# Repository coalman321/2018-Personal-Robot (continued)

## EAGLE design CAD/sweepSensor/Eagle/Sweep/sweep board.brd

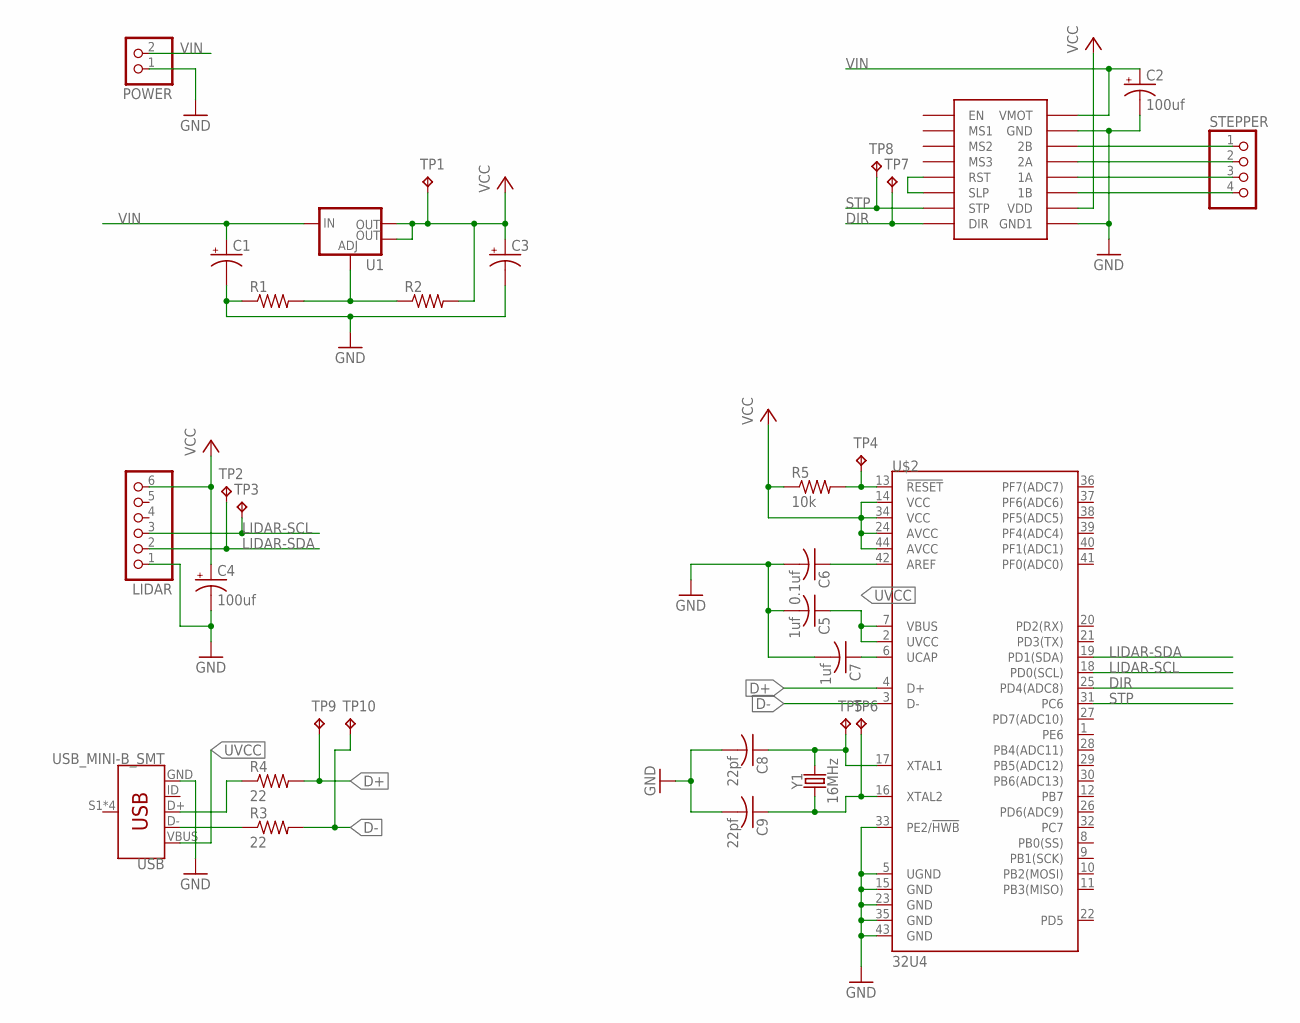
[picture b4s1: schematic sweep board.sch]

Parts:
C1: CPOL-USE2-5; E2-5
C2, C4: 100uf; E3,5-8
C3: CPOL-USE3.5-8; E3,5-8
C5, C7: 1uf; C0603
C6: 0.1uf; C0603
C8, C9: 22pf; C0603
LIDAR: PINHD-1X6; 1X06
POWER: PINHD-1X2; 1X02
R1, R2: R-US_R0603; R0603
R3, R4: 22; R0603
R5: 10k; R0603
STEPPER: PINHD-1X4; 1X04
TP1, TP2, TP3, TP4, TP5, TP6, TP7, TP8, TP9, TP10: TPB1,27; B1,27
U1: V_REG_LM1117SOT223; SOT223
U$1: A4988
U$2: 32U4; TQFP44
USB: USB_MINI-B_SMT; USB-MINIB
Y1: 16MHz; CRYSTAL-SMD-5X3.2-4PAD

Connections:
D+: R4.2, TP9.TP, U$2.4 (D+)
D-: R3.2, TP10.TP, U$2.3 (D-)
DIR: TP7.TP, U$1.P$8 (DIR), U$2.25 (PD4(ADC8))
GND: C1.-, C2.-, C3.-, C4.-, C5.2, C6.2, C7.2, C8.2, C9.2, LIDAR.1, POWER.1, R1.1, U$1.P$10 (GND), U$1.P$16 (GND1), U$2.5 (UGND), U$2.15 (GND), U$2.23 (GND), U$2.33 (PE2/!HWB), U$2.35 (GND), U$2.43 (GND), USB.GND
LIDAR-SCL: LIDAR.3, TP3.TP, U$2.18 (PD0(SCL))
LIDAR-SDA: LIDAR.2, TP2.TP, U$2.19 (PD1(SDA))
unnamed: U$1.P$5 (RST), U$1.P$6 (SLP)
unnamed: STEPPER.4, U$1.P$14 (1B)
unnamed: STEPPER.3, U$1.P$13 (1A)
unnamed: STEPPER.2, U$1.P$12 (2A)
unnamed: STEPPER.1, U$1.P$11 (2B)
unnamed: R3.1, USB.D-
unnamed: R4.1, USB.D+
unnamed: R1.2, R2.1, U1.1 (ADJ)
unnamed: R5.2, TP4.TP, U$2.13 (!RESET)
unnamed: C6.1, U$2.42 (AREF)
unnamed: C7.1, U$2.6 (UCAP)
unnamed: C9.1, TP6.TP, U$2.16 (XTAL2), Y1.1
unnamed: C8.1, TP5.TP, U$2.17 (XTAL1), Y1.3 (2)
STP: TP8.TP, U$1.P$7 (STP), U$2.31 (PC6)
UVCC: C5.1, U$2.2 (UVCC), U$2.7 (VBUS), USB.VBUS
VCC: C3.+, C4.+, LIDAR.6, R2.2, R5.1, TP1.TP, U1.2 (OUT), U1.4 (OUT), U$1.P$15 (VDD), U$2.14 (VCC), U$2.24 (AVCC), U$2.34 (VCC), U$2.44 (AVCC)
VIN: C1.+, C2.+, POWER.2, U1.3 (IN), U$1.P$9 (VMOT)

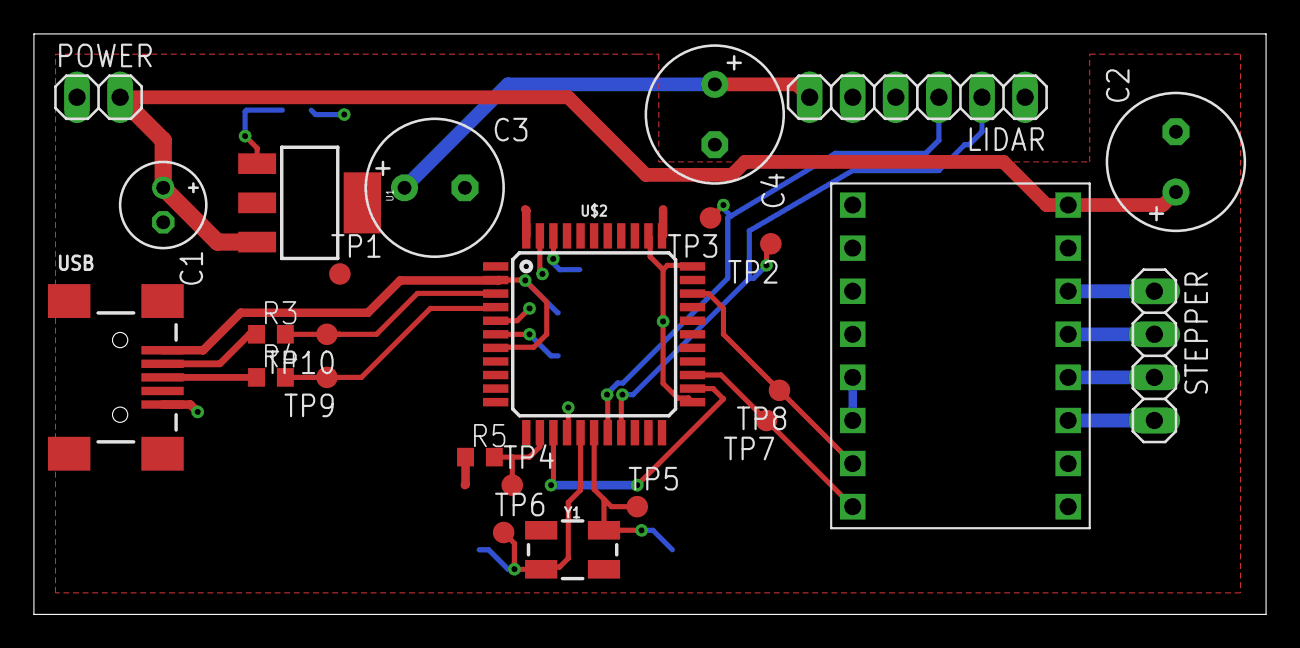
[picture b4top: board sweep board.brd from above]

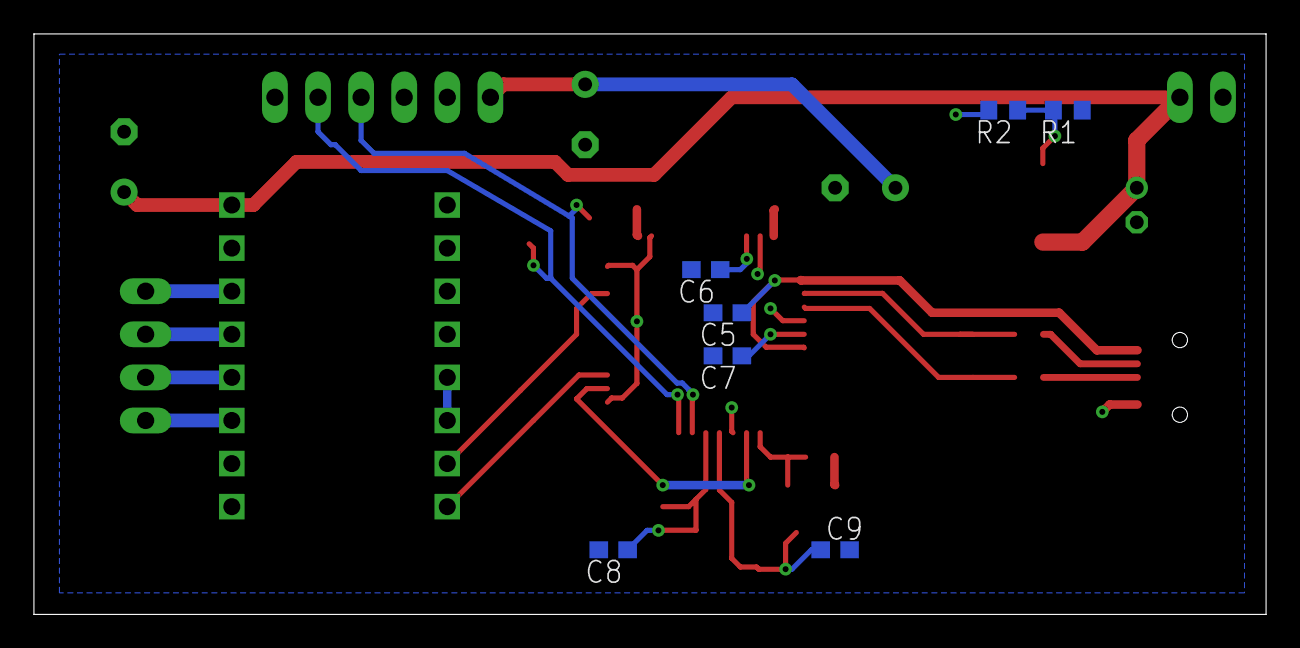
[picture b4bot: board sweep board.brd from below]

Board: 2 copper layers, 72.6 x 34.2 mm, 32 parts (7 on the bottom side), 23 nets.

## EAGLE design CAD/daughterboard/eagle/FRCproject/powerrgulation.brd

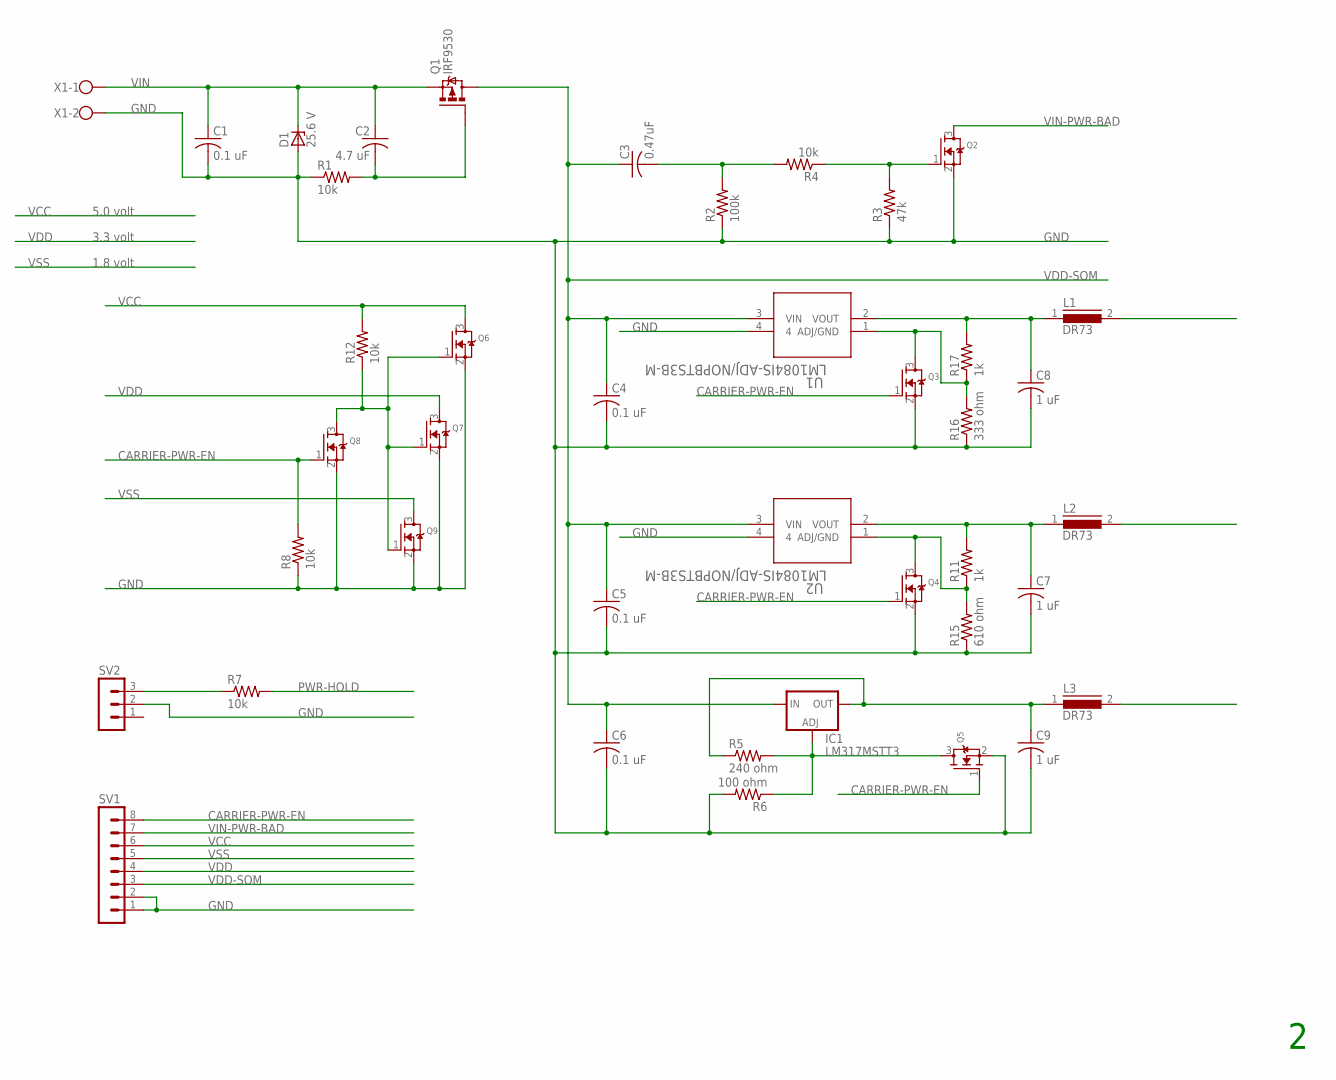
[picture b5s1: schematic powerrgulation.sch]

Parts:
C1, C4, C5, C6: 0.1 uF; C0805
C2: 4.7 uF; C0805
C3: 0.47uF; C0805
C7, C8, C9: 1 uF; C0805
D1: 25.6 V; SOT23
IC1: LM317MSTT3; SOT223
L1, L2, L3: DR73
Q1: IRF9530; TO220BV
Q2, Q3, Q4, Q5, Q6, Q7, Q8, Q9: MOSFET-NREFLOW; SOT23
R1, R4, R7, R8, R12: 10k; R0603
R2: 100k; R0603
R3: 47k; R0603
R5: 240 ohm; R0603
R6: 100 ohm; R0603
R11, R17: 1k; R0603
R15: 610 ohm; R0603
R16: 333 ohm; R0603
SV1: MA08-1
SV2: MA03-1
U1, U2: LM1084IS-ADJ/NOPBTS3B-M; TS3B-M
X1: W237-102

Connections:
CARRIER-PWR-EN: Q3.1 (G), Q4.1 (G), Q5.1 (G), Q8.1 (G), R8.2, SV1.8
GND: C1.2, C4.2, C5.2, C6.2, C7.2, C8.2, C9.2, D1.1 (A), Q2.2 (S), Q3.2 (S), Q4.2 (S), Q5.2 (S), Q6.2 (S), Q7.2 (S), Q8.2 (S), Q9.2 (S), R1.1, R2.1, R3.1, R6.2, R8.1, R15.1, R16.1, SV1.1, SV1.2, SV2.2, U1.4, U2.4, X1.2
unnamed: R7.1, SV2.3
unnamed: C3.2, R2.2, R4.2
unnamed: Q2.1 (G), R3.2, R4.1
unnamed: IC1.1 (ADJ), Q5.3 (D), R5.2, R6.1
unnamed: Q3.3 (D), R16.2, R17.1, U1.1 (ADJ/GND)
unnamed: Q4.3 (D), R11.1, R15.2, U2.1 (ADJ/GND)
PWR-HOLD: C2.2, Q1.G, R1.2, R7.2
RAIL-DISCHARGE: Q6.1 (G), Q7.1 (G), Q8.3 (D), Q9.1 (G), R12.1
VCC: L1.2, Q6.3 (D), R12.2, SV1.6
VCC-VOUT: C8.1, L1.1, R17.2, U1.2 (VOUT)
VDD: L2.2, Q7.3 (D), SV1.4
VDD-SOM: C3.1, C4.1, C5.1, C6.1, IC1.3 (IN), Q1.D, SV1.3, U1.3 (VIN), U2.3 (VIN)
VDD-VOUT: C7.1, L2.1, R11.2, U2.2 (VOUT)
VIN: C1.1, C2.1, D1.3 (C), Q1.S, X1.1
VIN-PWR-BAD: Q2.3 (D), SV1.7
VSS: L3.2, Q9.3 (D), SV1.5
VSS-VOUT: C9.1, IC1.4 (OUT), L3.1, R5.1

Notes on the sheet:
1.8 volt
3.3 volt
5.0 volt

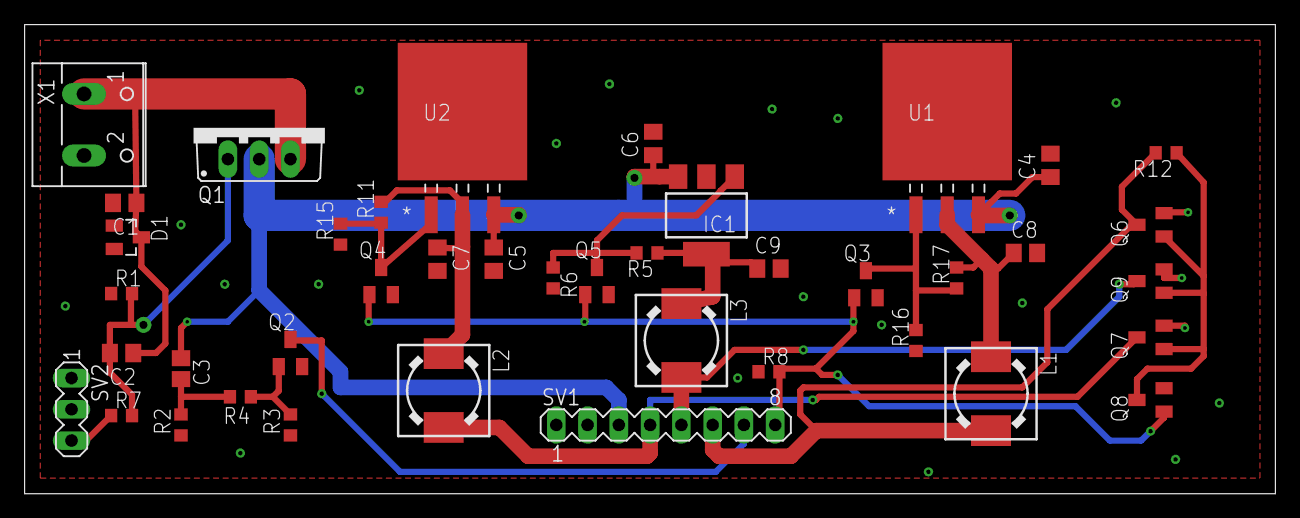
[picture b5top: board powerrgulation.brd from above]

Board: 2 copper layers, 101.6 x 38.1 mm, 41 parts (0 on the bottom side), 19 nets.

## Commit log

2018-05-23 added base project
2018-05-23 added PP code
2018-05-23 made logging system more robust for application
2018-05-25 minor patches
2018-05-26 setting up codebase
2018-08-07 added sim
2018-08-08 re-working rio code
2018-08-08 added beta code
2018-08-09 switching to 2018 system
2018-08-09 whaaaa
2018-08-09 project compiles
2018-08-09 compiles and tests!
2018-08-09 add subsystem manager
2018-08-10 ive got a theory. now to test its foundation
2018-08-11 removed trajectory generator test
2018-08-11 add cad folder
2018-08-14 reformatted and added looper control
2018-08-14 woops
2018-08-14 added subsystem manager calls to log and update info
2018-08-14 re-vamped OI
2018-08-15 further investigation of drive motion planner required
2018-08-17 cad files now openable & adding comments to drive motion planner
2018-08-19 added design doc and re-tooling DriveMotionPlanner
2018-08-20 gettting closer
    stripped drive motion planner of outputs. needs to be retooled next
    working on robot state to operate with ackerman chassis
2018-08-21 build & test completes
2018-08-21 added todo's
2018-08-21 added riemann sum for angular position from angular velocity
2018-08-22 added jetson code repo
2018-08-22 working on actual implementation of drive motion planner
2018-08-22 added example gnuplot scripts
2018-08-22 discovered bug in usage of output from drive motion planner
2018-08-23 Drive motion planner complete
    forward kinematics 2 is confirmed working and unit tests are back on
2018-08-23 added drive system test
2018-08-24 robot state estimation updated
2018-08-26 updated cad and added excel book
2018-08-27 update excel
2018-08-28 finishe drive cod except impl
2018-08-31 adding communications
2018-09-01 communication integration
2018-09-03 more tinkering with communication
2018-09-14 added docu
2019-01-06 add 2019 test code
2019-01-06 poke
2019-01-06 resource leaks & cleanup
2019-01-06 plenty of patches
2019-01-09 modulartity
2019-01-09 tested
2019-01-10 state machine tweaks to terminate
2019-01-10 state machine tweaks
2019-01-10 new drive system
2019-01-10 the big fix
2019-01-10 add driving actions
2019-01-10 hardware patches
2019-01-10 hardware patch part 2
2019-01-13 add new Sim
2019-01-14 continued development
    fixed UI
    added viewer ui
    began networking
2019-01-15 fix sim & added server
2019-01-15 remove unneeded empty string
2019-01-15 networking online
2019-01-16 a message
2019-01-17 tweak field
2019-01-17 proper scale & tweaks
2019-01-17 re-working ui
2019-01-19 stable with new development build
2019-01-20 add new robot parts
2019-01-20 add robot chassis and begin recording / playback
2019-01-20 Revert "add robot chassis and begin recording / playback"
    This reverts commit 09d94762e7d8077f52b68fdfa2565f654ed3f714.
2019-01-20 Revert "add new robot parts"
    This reverts commit 617b5b9a7d362eb2621e6ff0800a4ad9e1825744.
2019-01-20 ready for testing
2019-01-20 saving and loading works
2019-01-20 add ui loading & recording of files
2019-01-20 recording and playback from menu
2019-01-21 improved UI
2019-01-21 add rio pinging
2019-01-21 remove metadata
2019-01-21 tweak handshaking
2019-02-08 joints online
2019-04-05 popluate library files
2019-04-05 add basic subsystems
2019-04-06 add version plugin & refactor into math package
2019-04-06 working on socket tables client
    ther eis an issue with the server closing its connections after finishing
2019-04-06 data transfer bindings
2019-04-06 add socket timeouts
2019-04-06 add readwrite stamps
2019-04-06 add reflecting logger
2019-04-07 hahahahaha i winnnnnnn
2019-04-07 removed old loggers and renamed reflecting logger
2019-04-07 tweaks
2019-04-07 fixed naming scheme
2019-04-08 add time
2019-04-11 uncomment map re-build
2019-04-18 updated x
2019-05-05 new sim project
2019-05-05 add socket tables API to sim
2019-05-05 update data handler to be more dynamic
2019-05-08 updates to socket tables
2019-05-09 architectural updates
2019-05-10 getting places
    don't know where though
2019-05-19 switch to regex parsing
2019-05-26 Read optimized started
2019-05-26 read optimized is getting closer to completion
2019-05-27 fixed debug messages
2019-05-28 rework network helper
2019-06-01 move classes and create looper architecture
2019-06-09 switch to looper subsystem pattern for timing
